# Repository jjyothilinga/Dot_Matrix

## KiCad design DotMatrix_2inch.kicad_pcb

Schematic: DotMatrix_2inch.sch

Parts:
DS1, DS2, DS3, DS4, DS5, DS6, DS7, DS8: CMD-5571X00
P1, P2: CONN_24
P3, P7: CONN_8
P4, P5: CONN_2
P6: CONN_8X2
Q1, Q2, Q3, Q4, Q5, Q6, Q7: TIP127; TO220
R1, R2, R3, R4, R5, R6, R7: R

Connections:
/B1: P3.1, P6.1, R1.2
/B2: P3.2, P6.3, R2.2
/B3: P3.3, P6.5, R3.2
/B4: P3.4, P6.7, R4.2
/B5: P3.5, P6.9, R5.2
/B6: P3.6, P6.11, R6.2
/B7: P3.7, P6.13, R7.2
/C1: DS1.13, P1.1
/C2: DS1.3, P1.2
/C3: DS1.11, P1.3
/C4: DS1.10, P1.4
/C5: DS1.6, P1.5
/C6: DS2.13, P1.7
/C7: DS2.3, P1.8
/C8: DS2.11, P1.9
/C9: DS2.10, P1.10
/C10: DS2.6, P1.11
/C11: DS3.13, P1.13
/C12: DS3.3, P1.14
/C13: DS3.11, P1.15
/C14: DS3.10, P1.16
/C15: DS3.6, P1.17
/C16: DS4.13, P1.19
/C17: DS4.3, P1.20
/C18: DS4.11, P1.21
/C19: DS4.10, P1.22
/C20: DS4.6, P1.23
/C21: DS5.13, P2.1
/C22: DS5.3, P2.2
/C23: DS5.11, P2.3
/C24: DS5.10, P2.4
/C25: DS5.6, P2.5
/C26: DS6.13, P2.7
/C27: DS6.3, P2.8
/C28: DS6.11, P2.9
/C29: DS6.10, P2.10
/C30: DS6.6, P2.11
/C31: DS7.13, P2.13
/C32: DS7.3, P2.14
/C33: DS7.11, P2.15
/C34: DS7.10, P2.16
/C35: DS7.6, P2.17
/C36: DS8.13, P2.19
/C37: DS8.3, P2.20
/C38: DS8.11, P2.21
/C39: DS8.10, P2.22
/C40: DS8.6, P2.23
/R1: Q1.1 (B), R1.1
/R2: Q2.1 (B), R2.1
/R3: Q3.1 (B), R3.1
/R4: Q4.1 (B), R4.1
/R5: Q5.1 (B), R5.1
/R6: Q6.1 (B), R6.1
/R7: Q7.1 (B), R7.1
/ROW1: DS1.9, DS2.9, DS3.9, DS4.9, DS5.9, DS6.9, DS7.9, DS8.9, P6.2, P7.1, Q1.2 (C)
/ROW2: DS1.14, DS2.14, DS3.14, DS4.14, DS5.14, DS6.14, DS7.14, DS8.14, P6.4, P7.2, Q2.2 (C)
/ROW3: DS1.8, DS2.8, DS3.8, DS4.8, DS5.8, DS6.8, DS7.8, DS8.8, P6.6, P7.3, Q3.2 (C)
/ROW4: DS1.5, DS2.5, DS3.5, DS4.5, DS5.5, DS6.5, DS7.5, DS8.5, P6.8, P7.4, Q4.2 (C)
/ROW5: DS1.1, DS2.1, DS3.1, DS4.1, DS5.1, DS6.1, DS7.1, DS8.1, P6.10, P7.5, Q5.2 (C)
/ROW6: DS1.7, DS2.7, DS3.7, DS4.7, DS5.7, DS6.7, DS7.7, DS8.7, P6.12, P7.6, Q6.2 (C)
/ROW7: DS1.2, DS2.2, DS3.2, DS4.2, DS5.2, DS6.2, DS7.2, DS8.2, P6.14, P7.7, Q7.2 (C)
GND: P4.2 (PM), P5.2 (PM)
VCC: P4.1, P5.1, Q1.3 (E), Q2.3 (E), Q3.3 (E), Q4.3 (E), Q5.3 (E), Q6.3 (E), Q7.3 (E)

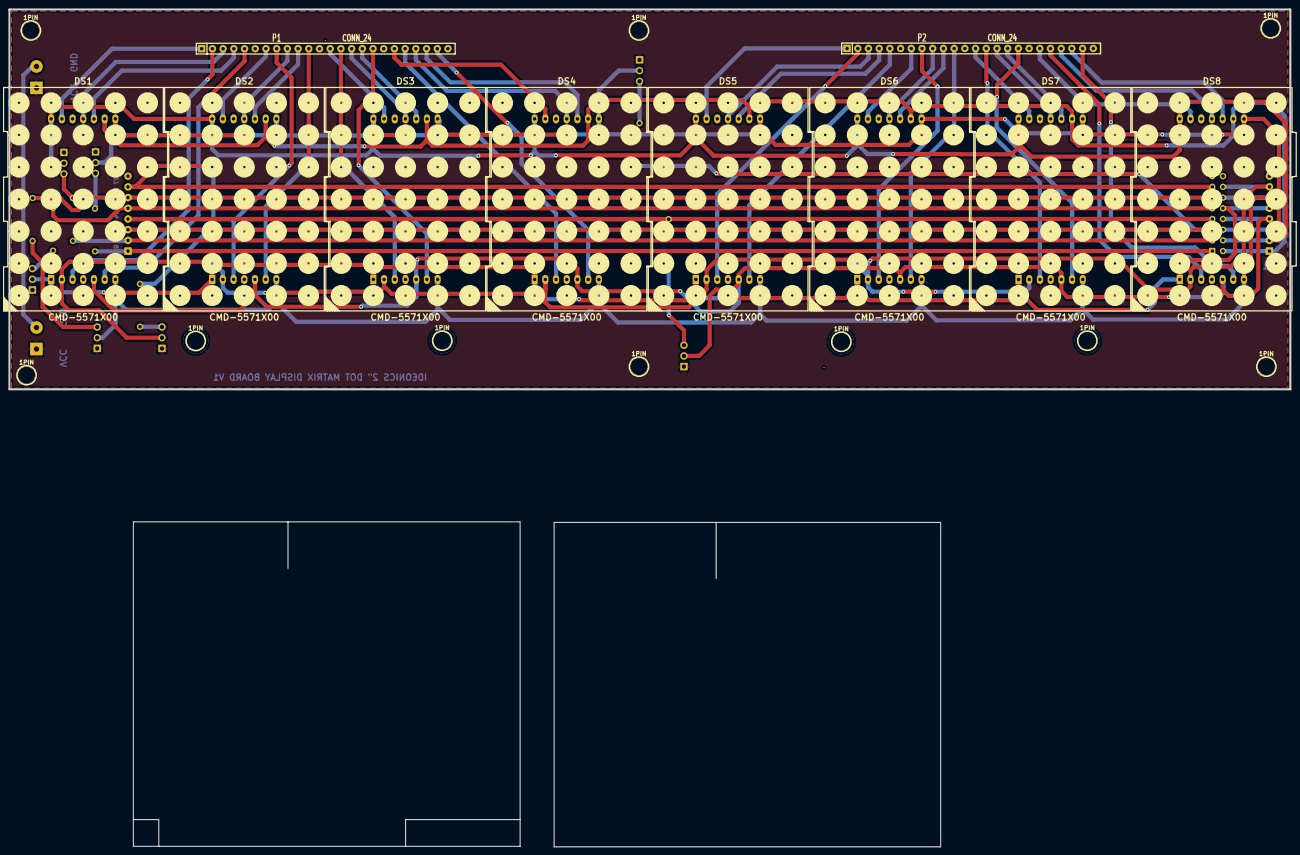
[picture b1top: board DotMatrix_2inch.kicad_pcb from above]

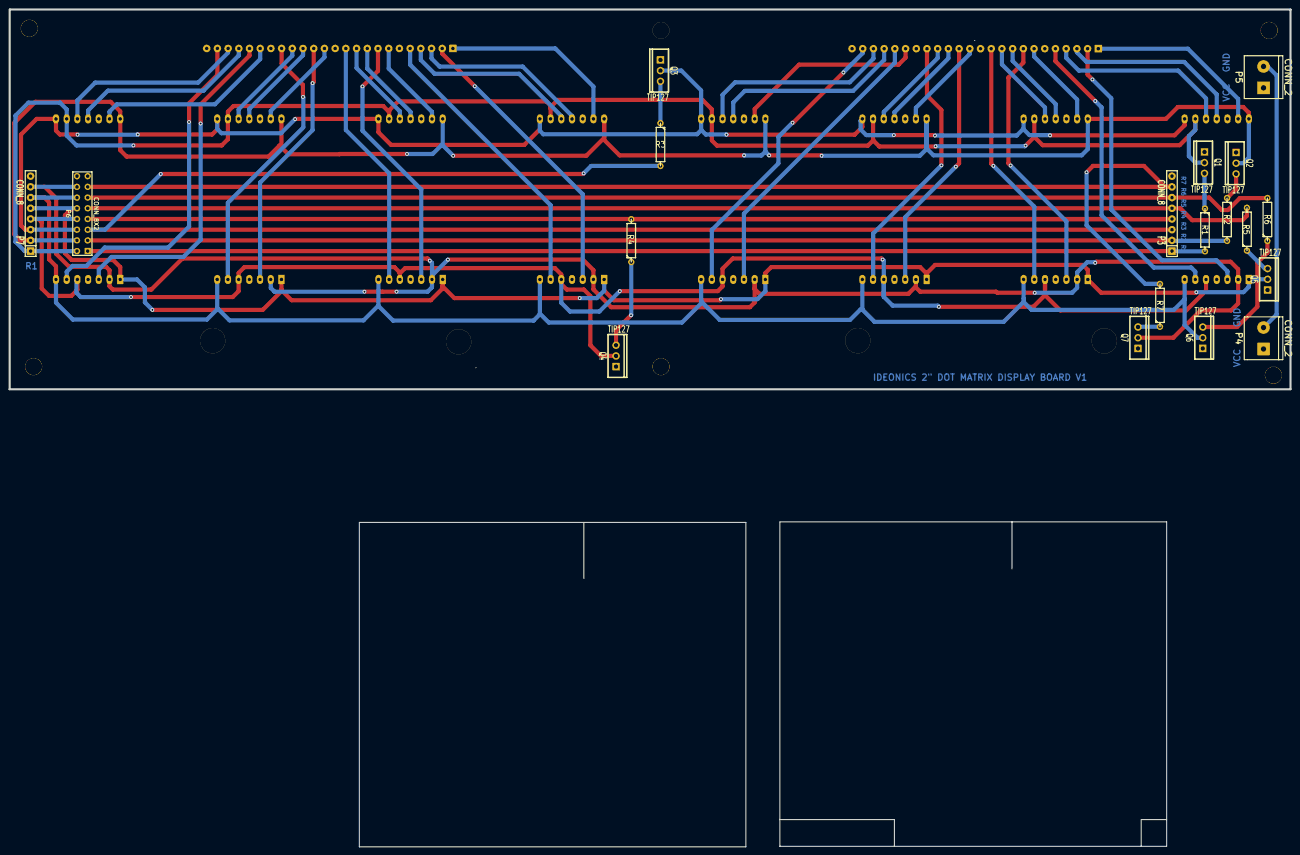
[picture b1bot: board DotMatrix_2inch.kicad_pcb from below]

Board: 2 copper layers, 303.9 x 90.1 mm, 39 parts (19 on the bottom side), 63 nets.

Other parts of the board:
1PIN, 1PIN#2, 1PIN#3, 1PIN#4, 1PIN#5, 1PIN#6, 1PIN#7, 1PIN#8, 1PIN#9, 1PIN#10: P***; 1pin

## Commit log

2014-11-25 :boom::camel: Added .gitattributes & .gitignore files
2015-04-15 Completed
